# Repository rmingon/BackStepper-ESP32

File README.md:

# BackStepper-ESP32

BackStepper-ESP32 is a custom control board that bolts onto the rear face of a NEMA17 stepper motor and embeds an ESP32 for closed-loop or network-connected motion projects. The PCB combines power regulation, a DRV8825 microstepping driver, and a USB-C interface so a single board can power, drive, and program the motor controller without additional wiring harnesses.

> Designed with KiCad 9.0 (2025 snapshot); all project files live under `hardware/`.

## Visuals

## Highlights

- ESP32-WROOM-32 module exposed for Wi-Fi/Bluetooth firmware as well as classic STEP/DIR motion control.
- DRV8825 stepper driver with 1/32 microstepping support and dedicated test pads on the STEP and DIR nets.
- CH340C USB-to-UART connected to a USB-C receptacle for flashing firmware and optionally powering the board.
- AMS1117-3.3 linear regulator fed from the +5 V plane to supply the ESP32 module and logic.
- JST-XH connectors for motor phases and the external 5 V feed, plus a 1×6 2.54 mm header for auxiliary serial access.
- Boot push-button on IO0 and CH340-controlled RTS/DTR FETs for hands-free flashing with `esptool.py`.
- Status LEDs on ESP32 IO12 and IO13 that can be repurposed for application feedback.
- Mounting hole pattern sized for the M3 boss spacing on a NEMA17 housing so the board can be screwed directly to the motor.

## Core Blocks

- **ESP32 module (`U2`)** – Provides dual-core MCU with Wi-Fi / BLE. STEP is on `IO4`, DIR on `IO5`, and UART0 is routed both to the CH340C and the breakout header.
- **Power regulation (`U3`)** – AMS1117-3.3 drops the shared +5 V plane down to 3.3 V for the ESP32 and CH340. Keep input below 6 V; logic and motor power are tied together on +5 V in this revision.
- **USB interface (`J2` + `U1`)** – USB-C receptacle wired for USB 2.0. CH340C handles the USB-to-UART bridge with RTS/DTR driving BSS138 FETs (`Q1`, `Q2`) to toggle EN and IO0 for automatic bootloader entry.
- **Stepper driver (`U4`)** – TI DRV8825 in HTSSOP package. Solder jumpers select the microstepping mode and sense resistor network sets coil current (see schematic for chosen values). Outputs route straight to the JST-XH motor connector.
- **User I/O** – `BTN1` pulls IO0 to ground for manual boot, status LEDs (`D1`, `D2`) sit on IO13 and IO12, and `TP1`/`TP2` break out STEP and DIR for probing or external drive injection.

## Connectors & Controls

| Ref  | Type / Pitch | Pinout (1 → n) | Notes |
|------|--------------|----------------|-------|
| `J2` | USB-C (USB 2.0) | VBUS, D-, D+, CC1/CC2, shield | Powers CH340C/ESP32 from 5 V VBUS and provides the programming link. |
| `J4` | JST-XH 1×2 vertical | 1: GND · 2: +5 V | Primary power input. In this design +5 V feeds both DRV8825 VMOT and the AMS1117 regulator. |
| `J3` | JST-XH 1×4 vertical | 1: AOUT2 · 2: AOUT1 · 3: BOUT1 · 4: BOUT2 | Connect the stepper phases A/B (watch the order to match motor datasheet). |
| `J1` | 1×6 2.54 mm header | 1: NC · 2: RX0 · 3: TX0 · 4: +5 V · 5: NC · 6: GND | Aux UART header for programming/debug or external peripherals. |
| `BTN1` | Tactile push-button | IO0 ↔ GND | Forces the ESP32 boot pin low; use with EN toggle to enter download mode. |
| `TP1` | Test pad | STEP | Logic probe / scope pad tied to DRV8825 STEP and ESP32 IO4. |
| `TP2` | Test pad | DIR | Logic probe / scope pad tied to DRV8825 DIR and ESP32 IO5. |

## Microstepping Jumpers

Three solder jumpers strap DRV8825 `MODE0..2`. Each jumper has **GND** on the silkscreened dot side (pad A) and **3.3 V** on the opposite side (pad B). Leaving a jumper open lets the DRV8825’s internal pulldown pull the mode low.

| Microstep mode | `JP1` (MODE0) | `JP2` (MODE1) | `JP3` (MODE2) |
|----------------|---------------|---------------|---------------|
| Full step      | open (low)    | open (low)    | open (low)    |
| 1/2 step       | short to 3.3 V| open          | open          |
| 1/4 step       | open          | short to 3.3 V| open          |
| 1/8 step       | short to 3.3 V| short to 3.3 V| open          |
| 1/16 step      | open          | open          | short to 3.3 V|
| 1/32 step      | short to 3.3 V| open          | short to 3.3 V|
| 1/32 step      | open          | short to 3.3 V| short to 3.3 V|
| 1/32 step      | short to 3.3 V| short to 3.3 V| short to 3.3 V|

Reflow a small solder bridge between the center pad and the desired side to change the logic level. Remove bridges with solder wick when changing configuration.

## Powering and Using the Board

1. **Supply** – Feed +5 V either through the USB-C port (VBUS) or the `J4` JST connector. Because the DRV8825 VM pins are tied to +5 V, this revision targets low-voltage steppers; do not exceed 5–6 V on the supply without redesigning the power stage.
2. **Motor hookup** – Wire the stepper to `J3`. If the motor runs rough, swap pins within a phase pair to keep coil polarity consistent.
3. **Programming** – Connect USB-C to your PC. The CH340C enumerates as a serial port. `esptool.py` can reset the ESP32 automatically via RTS/DTR. Use `BTN1` only if manual boot selection is needed.
4. **Firmware** – STEP/DIR live on IO4/IO5; UART1 (IO19/IO21) is broken out internally if you need another serial channel. LEDs on IO12/IO13 provide quick visual feedback.

Current sense resistors and VREF test points are accessible near the driver; tune current following the DRV8825 datasheet.

## Repository Layout

- `hardware/` – KiCad project (`.pro`, `.sch`, `.kicad_pcb`) plus backup caches.
- `Capture d’écran *.png` – Draft renders / screenshots of the PCB as designed in the IDE.

Generate manufacturing outputs from KiCad (`File → Fabrication Outputs`) against the `hardware.kicad_pro` project once component values are finalised.

## License

This project is released under the **CERN Open Hardware Licence v2 Strongly Reciprocal (CERN-OHL-S-2.0)**. See the `LICENSE` file for the full text and your obligations when modifying or distributing the design or fabricated hardware.

## Next Steps

- Add a dedicated EN/RESET push-button if manual resets become necessary.
- Consider isolating motor and logic rails or moving to a higher-voltage supply for more torque.
- Document tested firmware builds and pin assignments once the mechanical integration is validated.

Feel free to open issues or PRs as the design evolves. Happy hacking!

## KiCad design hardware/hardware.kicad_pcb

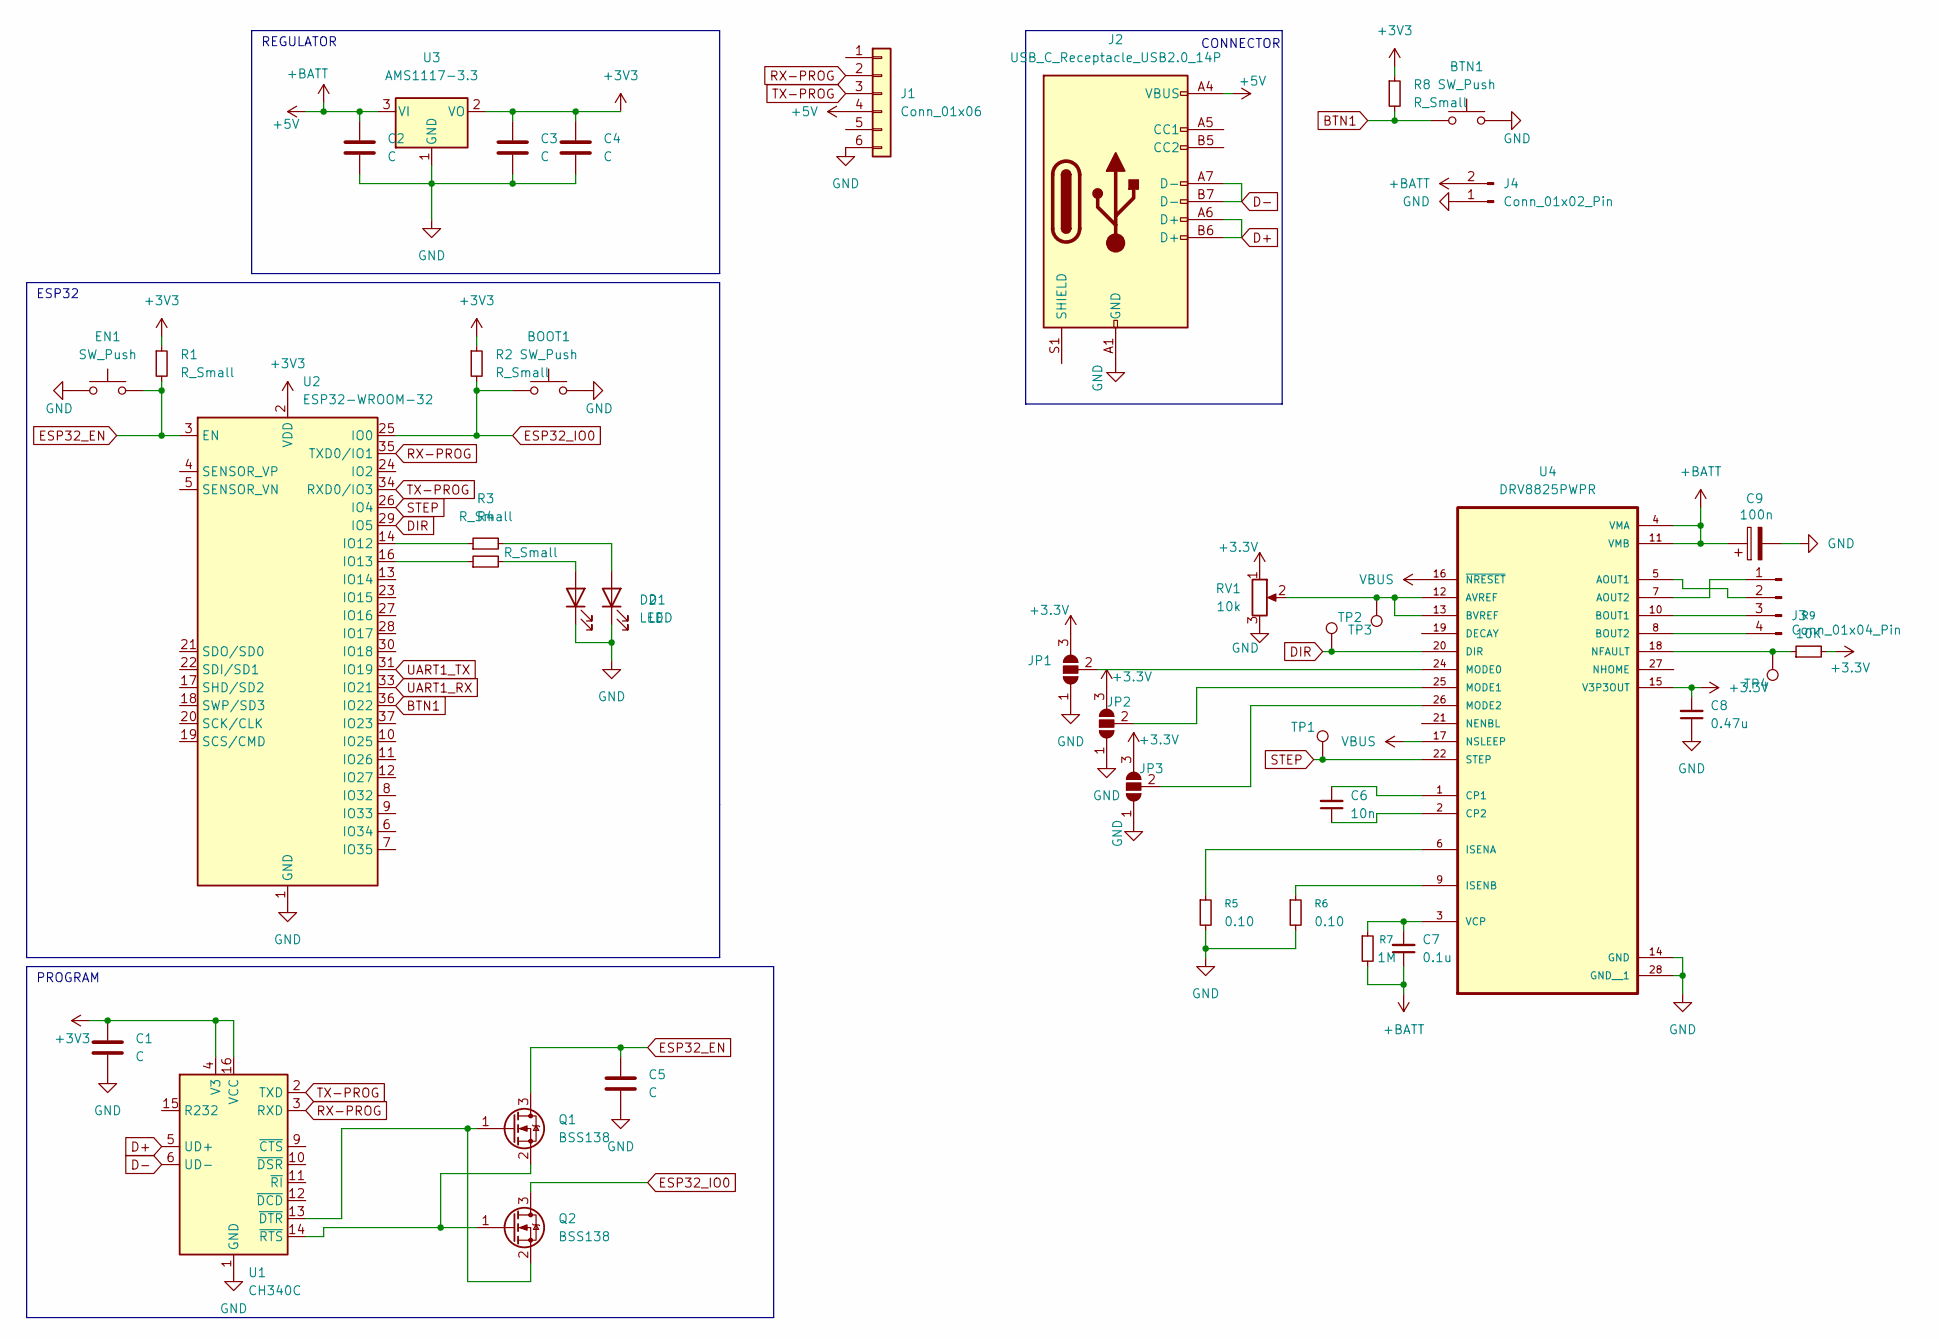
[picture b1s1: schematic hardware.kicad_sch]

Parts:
BOOT1: SW_Push; SW_Push_SPST_NO_Alps_SKRK; LCSC C398053
BTN1: SW_Push; SW_Push_SPST_NO_Alps_SKRK; LCSC C398053
C1, C2, C4: C; C_0603_1608Metric; LCSC C30926
C3, C5: C; C_0603_1608Metric; LCSC C19702
C6: 10n; C_0603_1608Metric
C7: 0.1u; C_0603_1608Metric
C8: 0.47u; C_0603_1608Metric
C9: 100n; CP_Elec_6.3x5.7
D1: LED; LED_0603_1608Metric; LCSC C19171301
D2: LED; LED_0603_1608Metric; LCSC C434425
EN1: SW_Push; SW_Push_SPST_NO_Alps_SKRK; LCSC C398053
J1: Conn_01x06; PinHeader_1x06_P2.54mm_Vertical
J2: USB_C_Receptacle_USB2.0_14P; USB_C_Receptacle_JAE_DX07S016JA1R1500; LCSC C963213
J3: Conn_01x04_Pin; JST_XH_B4B-XH-A_1x04_P2.50mm_Vertical
J4: Conn_01x02_Pin; JST_XH_B2B-XH-A_1x02_P2.50mm_Vertical
JP1, JP2, JP3: SolderJumper_3_Open; SolderJumper-3_P1.3mm_Open_RoundedPad1.0x1.5mm
Q1, Q2: BSS138; SOT-23; LCSC C7420338
R1, R2, R8: R_Small; R_0603_1608Metric; LCSC C98220
R3, R4: R_Small; R_0603_1608Metric; LCSC C2906975
R5, R6: 0.10; R_0603_1608Metric
R7: 1M; R_0603_1608Metric
R9: 10K; R_0603_1608Metric
RV1: 10k; Potentiometer_Bourns_3214J_Horizontal
TP1, TP2, TP3, TP4: TestPoint; TestPoint_Pad_1.5x1.5mm
U1: CH340C; SOIC-16_3.9x9.9mm_P1.27mm; LCSC C84681
U2: ESP32-WROOM-32; LCSC C82899
U3: AMS1117-3.3; SOT-223-3_TabPin2; LCSC C6186
U4: DRV8825PWPR; IC_TPS61196PWPRQ1

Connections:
+3.3V: C8.2, JP1.3 (B), JP2.3 (B), JP3.3 (B), R9.2, RV1.1, U4.15 (V3P3OUT)
+3V3: C1.1, C3.1, C4.1, R1.1, R2.1, R8.1, U1.4 (V3), U1.16 (VCC), U2.2 (VDD), U3.2 (VO)
+5V: C2.1, C7.1, C9.1, J1.4, J2.A4 (VBUS), J2.A9 (VBUS), J2.B4 (VBUS), J2.B9 (VBUS), J4.2, R7.2, U3.3 (VI), U4.4 (VMA), U4.11 (VMB)
BTN1: BTN1.1, R8.2, U2.36 (IO22)
D+: J2.A6 (D+), J2.B6 (D+), U1.5 (UD+)
D-: J2.A7 (D-), J2.B7 (D-), U1.6 (UD-)
DIR: TP2.1, U2.29 (IO5), U4.20 (DIR)
ESP32_EN: C5.1, EN1.2, Q1.3 (D), R1.2, U2.3 (EN)
ESP32_IO0: BOOT1.1, Q2.3 (D), R2.2, U2.25 (IO0)
GND: BOOT1.2, BTN1.2, C1.2, C2.2, C3.2, C4.2, C5.2, C8.1, C9.2, D1.1 (K), D2.1 (K), EN1.1, J1.6, J2.A1 (GND), J2.A12 (GND), J2.B1 (GND), J2.B12 (GND), J4.1, JP1.1 (A), JP2.1 (A), JP3.1 (A), R5.2, R6.2, RV1.3, U1.1 (GND), U2.1 (GND), U2.15 (GND), U2.38 (GND), U2.39 (GND), U3.1 (GND), U4.14 (GND), U4.28 (GND__1)
unnamed: D1.2 (A), R4.2
unnamed: D2.2 (A), R3.2
unnamed: J3.1, U4.7 (AOUT2)
unnamed: J3.2, U4.5 (AOUT1)
unnamed: J3.3, U4.10 (BOUT1)
unnamed: J3.4, U4.8 (BOUT2)
unnamed: JP1.2 (C), U4.24 (MODE0)
unnamed: JP2.2 (C), U4.25 (MODE1)
unnamed: JP3.2 (C), U4.26 (MODE2)
unnamed: Q1.1 (G), Q2.2 (S), U1.13 (~DTR)
unnamed: Q1.2 (S), Q2.1 (G), U1.14 (~RTS)
unnamed: R3.1, U2.14 (IO12)
unnamed: R4.1, U2.16 (IO13)
unnamed 23: RV1.2, TP3.1, U4.12 (AVREF), U4.13 (BVREF); also elsewhere on the board
unnamed: C6.2, U4.1 (CP1)
unnamed: C6.1, U4.2 (CP2)
unnamed: R5.1, U4.6 (ISENA)
unnamed: R6.1, U4.9 (ISENB)
unnamed 28: R9.1, TP4.1, U4.18 (NFAULT); also elsewhere on the board
unnamed: C7.2, R7.1, U4.3 (VCP)
RX-PROG: J1.2, U1.3 (RXD), U2.35 (TXD0/IO1)
STEP: TP1.1, U2.26 (IO4), U4.22 (STEP)
TX-PROG: J1.3, U1.2 (TXD), U2.34 (RXD0/IO3)
UART1_RX: U2.33 (IO21)
UART1_TX: U2.31 (IO19)
VBUS: U4.16 (~NRESET), U4.17 (NSLEEP)

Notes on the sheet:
REGULATOR
ESP32
PROGRAM
CONNECTOR

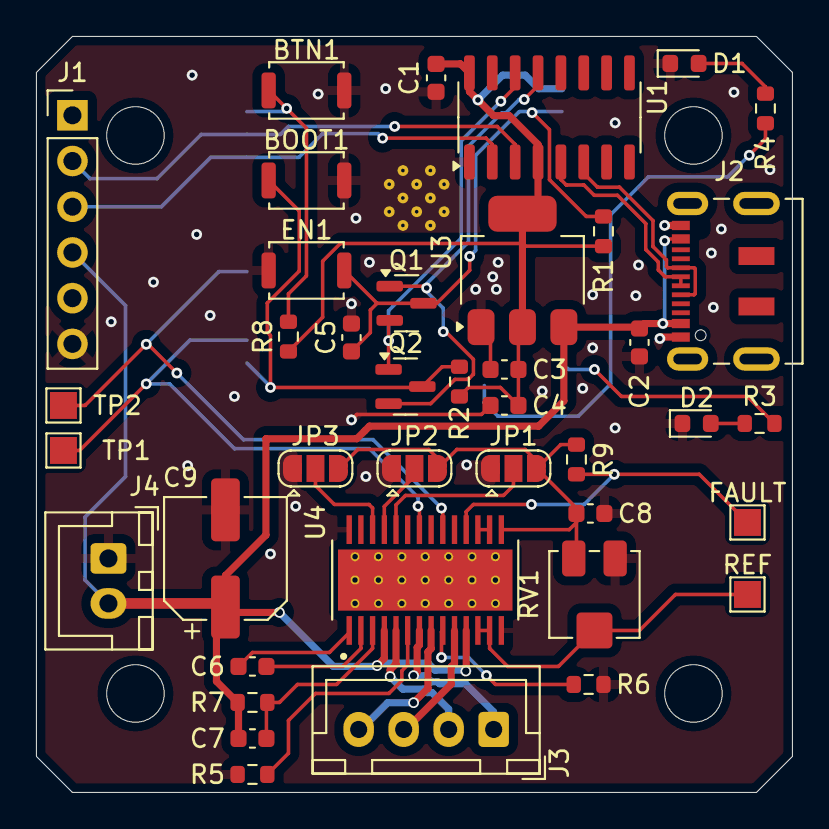
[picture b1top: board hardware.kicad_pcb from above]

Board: 2 copper layers, 42.0 x 42.0 mm, 41 parts (1 on the bottom side), 34 nets.

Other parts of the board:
FAULT: TestPoint; TestPoint_Pad_1.5x1.5mm
REF: TestPoint; TestPoint_Pad_1.5x1.5mm

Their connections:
unnamed 23: REF.1; also elsewhere on the board
unnamed 28: FAULT.1; also elsewhere on the board

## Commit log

2025-10-22 add schematic
2025-10-22 add pcb size for nema17
2025-10-22 finish pcb wiring
2025-10-22 add picture
2025-10-22 add licence
2025-10-22 add readme
2025-10-22 add pictures
2025-10-24 gnd capacitor pcb wiring
